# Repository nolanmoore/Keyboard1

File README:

# Keyboard1

This is keyboard project #1, a semi ortholinear board designed to replace the standard Let's Split lefthand board. It is designed to replace the bottom row with ANSI standard 1.25u modifiers and space bar, leaving a single 1u key for "Raise."

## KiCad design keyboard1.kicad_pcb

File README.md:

# Keyboard1

This is keyboard project #1, a semi ortholinear board designed to replace the standard Let's Split lefthand board. It is designed to replace the bottom row with ANSI standard 1.25u modifiers and space bar, leaving a single 1u key for "Raise."

Libraries for the MX switches and other components sourced from mechkeys' [mechkeys repo](https://github.com/mechkeys/mechkeys).

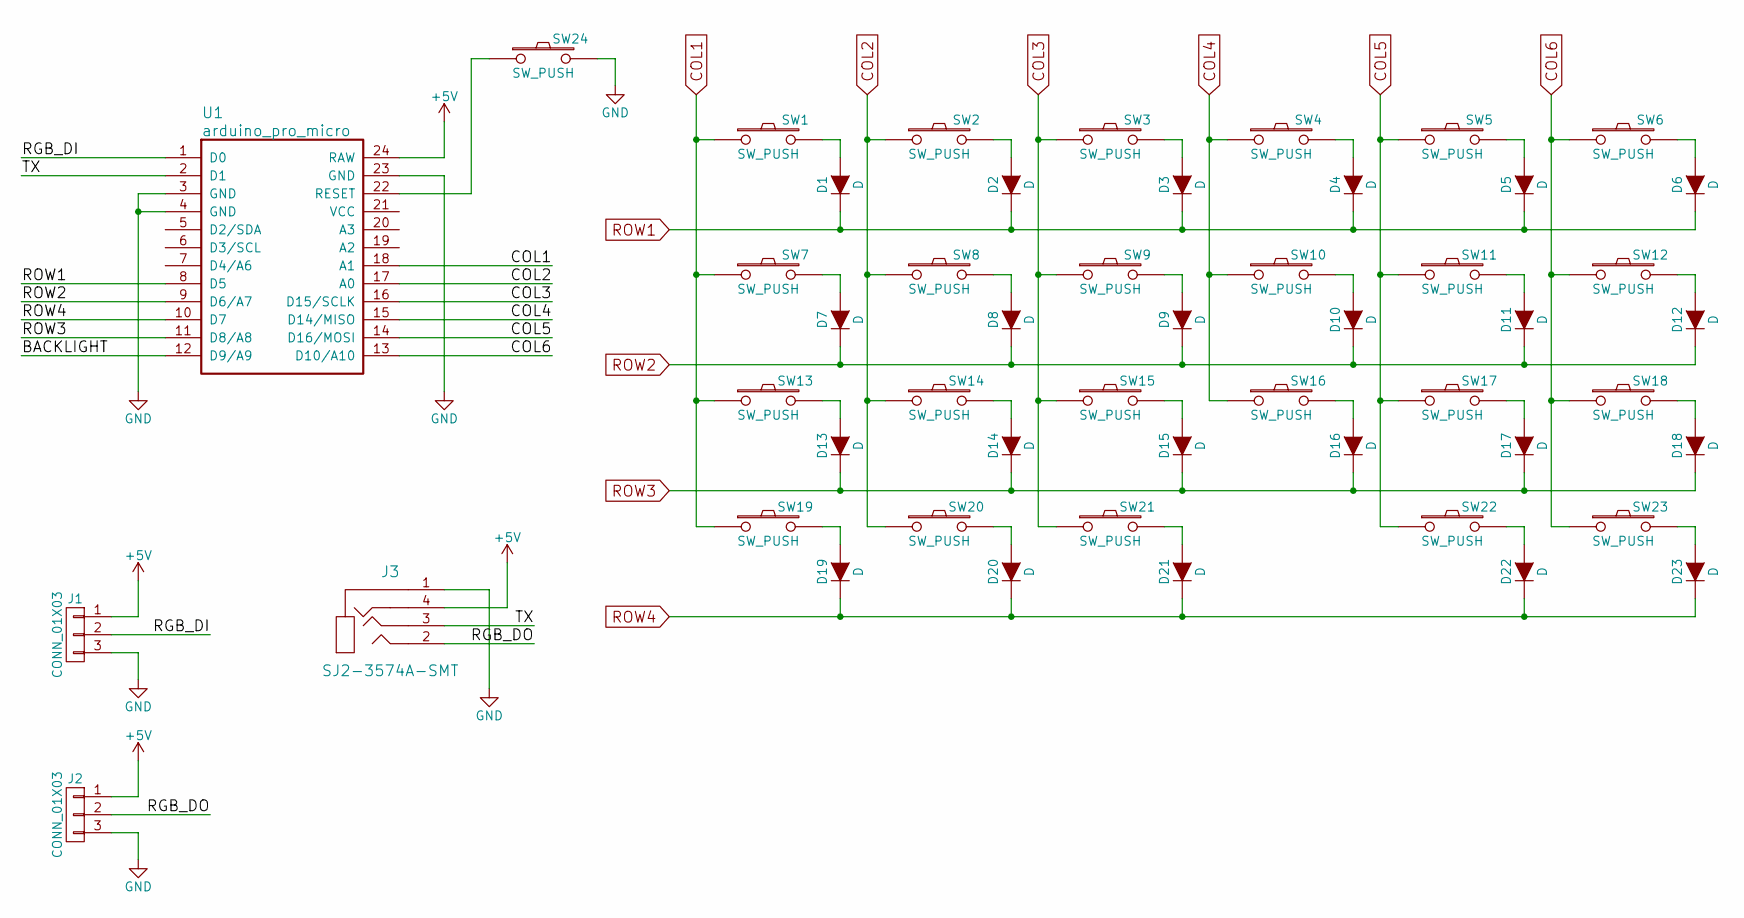
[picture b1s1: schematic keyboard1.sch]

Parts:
D1, D2, D3, D4, D5, D6, D7, D8, D9, D10, D11, D12, D13, D14, D15, D16, D17, D18, D19, D20, D21, D22, D23: D; DIODE
J1, J2: CONN_01X03; WS2812_3PIN
J3: SJ2-3574A-SMT
SW1, SW2, SW3, SW4, SW5, SW6, SW7, SW8, SW9, SW10, SW11, SW12, SW13, SW14, SW15, SW16, SW17, SW18: SW_PUSH; CHERRY_PCB_100H
SW19, SW20, SW21, SW22, SW23: SW_PUSH; CHERRY_PCB_125H
SW24: SW_PUSH; SW_SPST_EVQP7C
U1: arduino_pro_micro; arduino-pro-micro

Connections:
+5V: J1.1, J2.1, J3.4, U1.24 (RAW)
/BACKLIGHT: U1.12 (D9/A9)
/RGB_DI: J1.2, U1.1 (D0)
/RGB_DO: J2.2, J3.2
/TX: J3.3, U1.2 (D1)
COL1: SW1.1, SW7.1, SW13.1, SW19.1, U1.18 (A1)
COL2: SW2.1, SW8.1, SW14.1, SW20.1, U1.17 (A0)
COL3: SW3.1, SW9.1, SW15.1, SW21.1, U1.16 (D15/SCLK)
COL4: SW4.1, SW10.1, SW16.1, U1.15 (D14/MISO)
COL5: SW5.1, SW11.1, SW17.1, SW22.1, U1.14 (D16/MOSI)
COL6: SW6.1, SW12.1, SW18.1, SW23.1, U1.13 (D10/A10)
GND: J1.3, J2.3, J3.1, SW24.2, U1.3 (GND), U1.4 (GND), U1.23 (GND)
unnamed: D1.2 (A), SW1.2
unnamed: D2.2 (A), SW2.2
unnamed: D3.2 (A), SW3.2
unnamed: D4.2 (A), SW4.2
unnamed: D5.2 (A), SW5.2
unnamed: D6.2 (A), SW6.2
unnamed: D7.2 (A), SW7.2
unnamed: D8.2 (A), SW8.2
unnamed: D9.2 (A), SW9.2
unnamed: D10.2 (A), SW10.2
unnamed: D11.2 (A), SW11.2
unnamed: D12.2 (A), SW12.2
unnamed: D13.2 (A), SW13.2
unnamed: D14.2 (A), SW14.2
unnamed: D15.2 (A), SW15.2
unnamed: D16.2 (A), SW16.2
unnamed: D17.2 (A), SW17.2
unnamed: D18.2 (A), SW18.2
unnamed: D19.2 (A), SW19.2
unnamed: D20.2 (A), SW20.2
unnamed: D21.2 (A), SW21.2
unnamed: D22.2 (A), SW22.2
unnamed: D23.2 (A), SW23.2
unnamed: SW24.1, U1.22 (RESET)
ROW1: D1.1 (K), D2.1 (K), D3.1 (K), D4.1 (K), D5.1 (K), D6.1 (K), U1.8 (D5)
ROW2: D7.1 (K), D8.1 (K), D9.1 (K), D10.1 (K), D11.1 (K), D12.1 (K), U1.9 (D6/A7)
ROW3: D13.1 (K), D14.1 (K), D15.1 (K), D16.1 (K), D17.1 (K), D18.1 (K), U1.11 (D8/A8)
ROW4: D19.1 (K), D20.1 (K), D21.1 (K), D22.1 (K), D23.1 (K), U1.10 (D7)

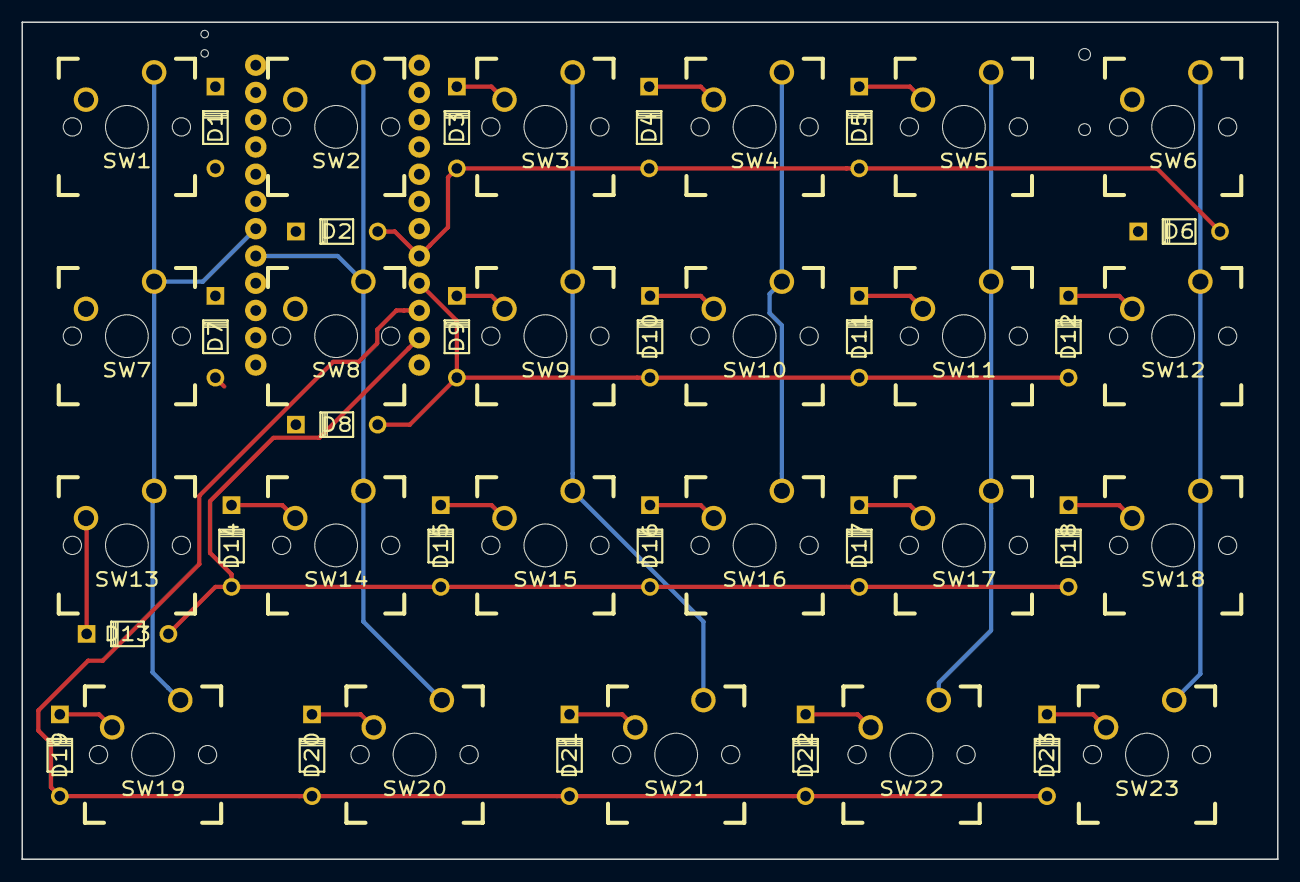
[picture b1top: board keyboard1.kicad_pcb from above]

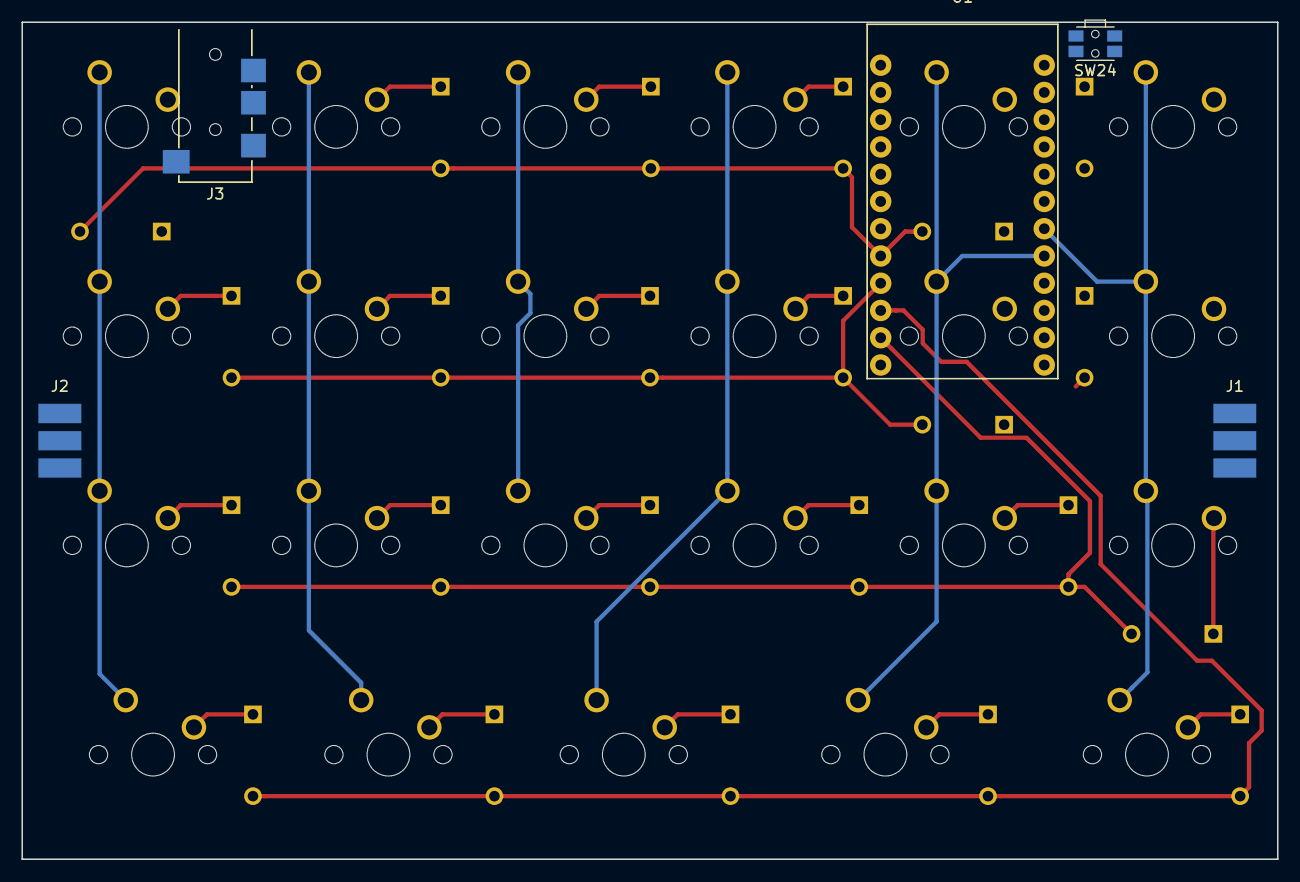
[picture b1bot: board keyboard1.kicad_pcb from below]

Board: 2 copper layers, 117.0 x 78.0 mm, 51 parts (5 on the bottom side), 39 nets.

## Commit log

2017-10-19 Basic schematic complete, routing in progress
2017-10-19 minor readme update
2017-10-19 Rename README to README.md
2017-10-19 Added KLE preview to readme
